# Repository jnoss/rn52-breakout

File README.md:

# rn52-breakout
RN-52 breakout board (Based on Sparkfun's, but adds FTDI header)

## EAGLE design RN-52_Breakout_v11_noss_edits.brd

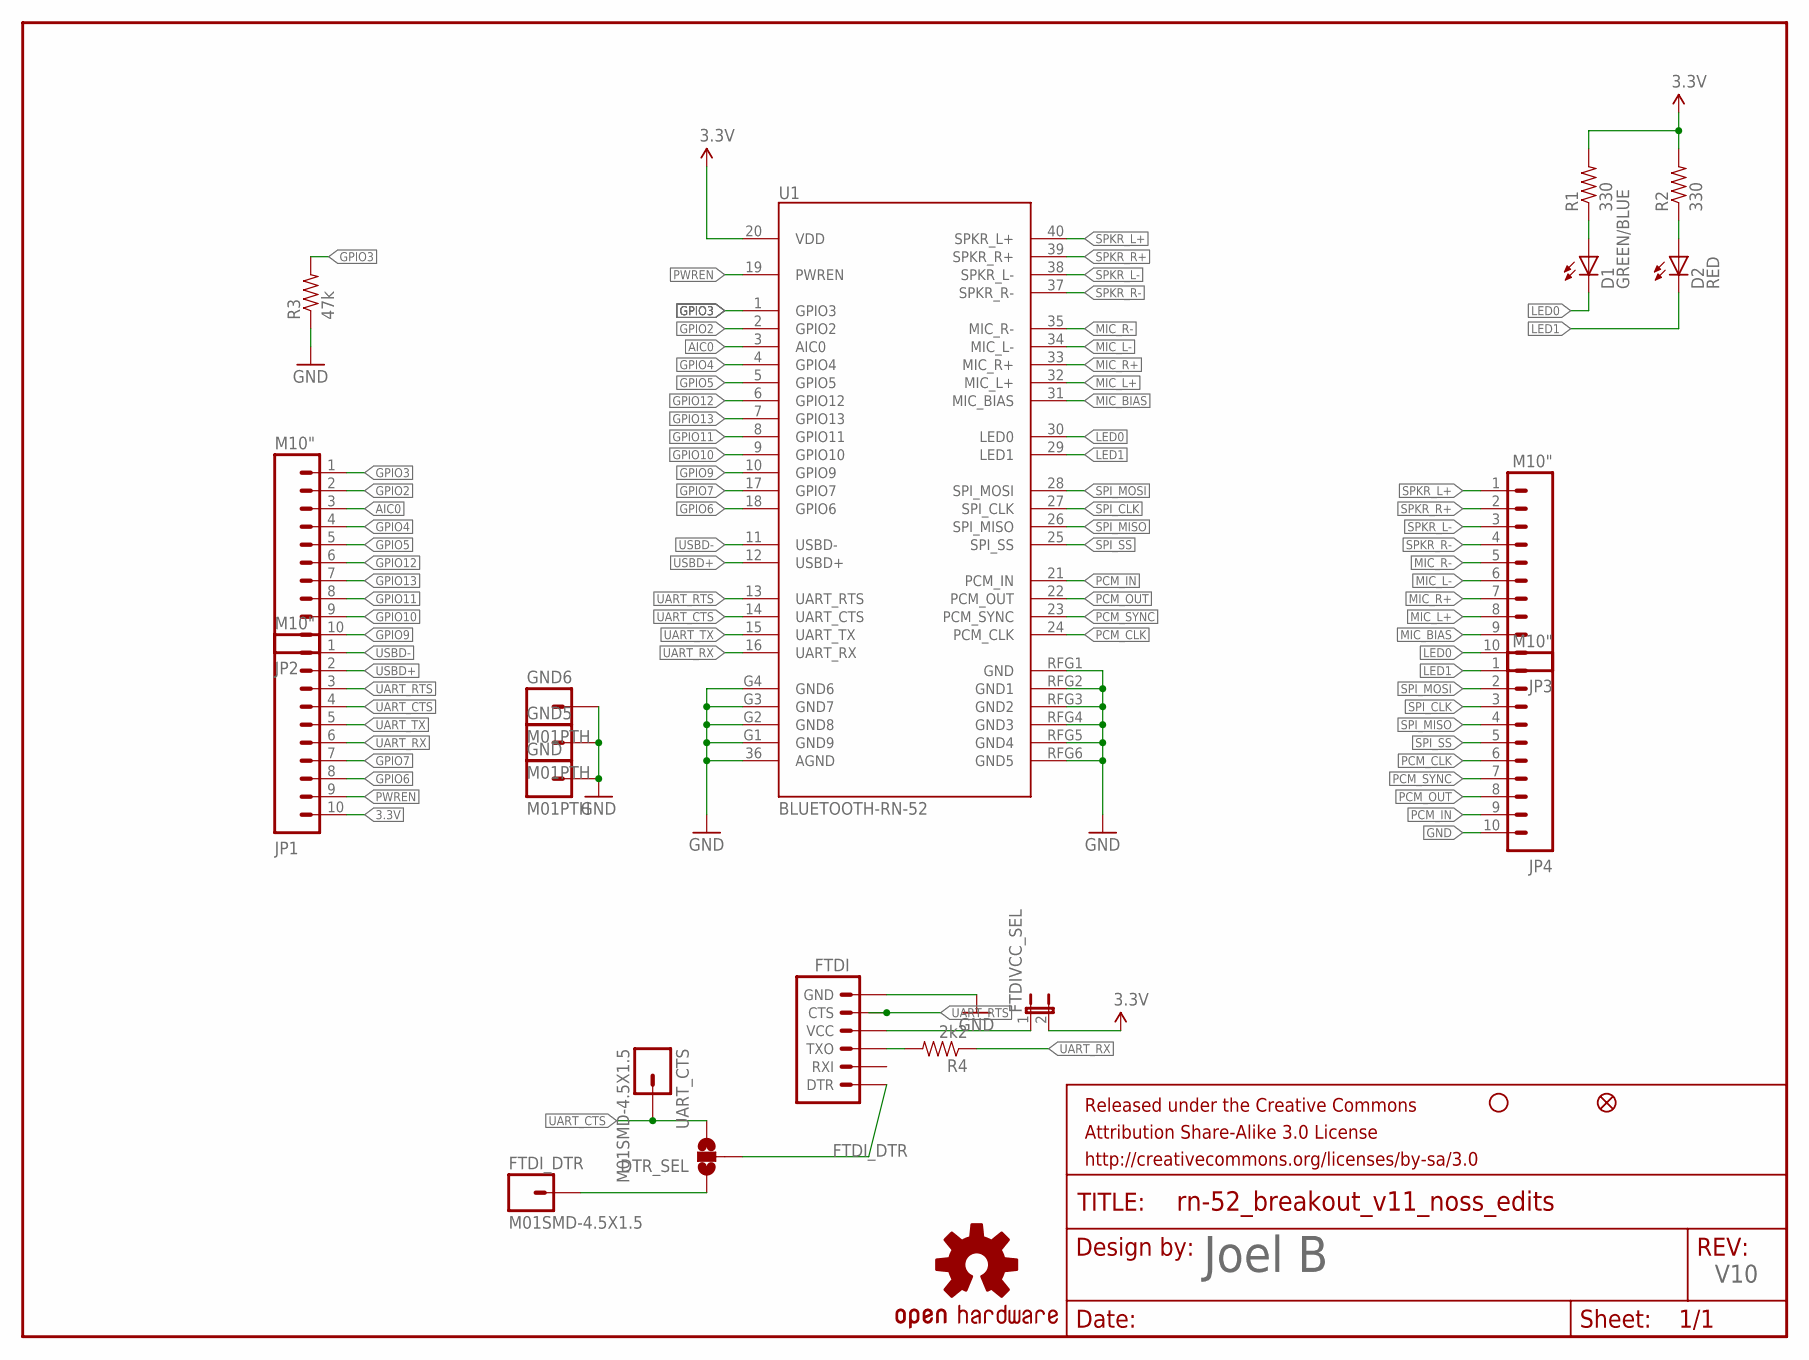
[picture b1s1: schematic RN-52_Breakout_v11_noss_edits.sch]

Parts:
D1: GREEN/BLUE; LED-0603
D2: RED; LED-0603
DTR_SEL: SOLDERJUMPER_2WAYS; SJ_3
FID1: FIDUCIAL1X2; FIDUCIAL-1X2
FRAME1: FRAME-LETTER; CREATIVE_COMMONS
FTDI: ARDUINO_SERIAL_PROGRAMPTH; 1X06
FTDIVCC_SEL: JUMPER-2PTH; 1X02
FTDI_DTR: M01SMD-4.5X1.5; PAD-1.5X4.5
GND, GND5, GND6: M01PTH; 1X01
JP1, JP2, JP3, JP4: M10"; 1X10
LOGO1: OSHW-LOGOS; OSHW-LOGO-S
R1, R2: 330; 0603-RES
R3: 47k; 0603-RES
R4: 2k2; 0603-RES
STANDOFF1: STAND-OFF
U1: BLUETOOTH-RN-52; RN-52
UART_CTS: M01SMD-4.5X1.5; PAD-1.5X4.5

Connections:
3.3V: FTDIVCC_SEL.2, JP1.10, R1.2, R2.2, U1.20 (VDD)
AIC0: JP2.3, U1.3 (AIC0)
FTDI_DTR: DTR_SEL.2, FTDI.1 (DTR)
GND: FTDI.6 (GND), GND.1, GND5.1, GND6.1, JP4.10, R3.1, U1.36 (AGND), U1.G1 (GND9), U1.G2 (GND8), U1.G3 (GND7), U1.G4 (GND6), U1.RFG1 (GND), U1.RFG2 (GND1), U1.RFG3 (GND2), U1.RFG4 (GND3), U1.RFG5 (GND4), U1.RFG6 (GND5)
GPIO2: JP2.2, U1.2 (GPIO2)
GPIO3: JP2.1, R3.2, U1.1 (GPIO3)
GPIO4: JP2.4, U1.4 (GPIO4)
GPIO5: JP2.5, U1.5 (GPIO5)
GPIO6: JP1.8, U1.18 (GPIO6)
GPIO7: JP1.7, U1.17 (GPIO7)
GPIO9: JP2.10, U1.10 (GPIO9)
GPIO10: JP2.9, U1.9 (GPIO10)
GPIO11: JP2.8, U1.8 (GPIO11)
GPIO12: JP2.6, U1.6 (GPIO12)
GPIO13: JP2.7, U1.7 (GPIO13)
LED0: D1.C, JP3.10, U1.30 (LED0)
LED1: D2.C, JP4.1, U1.29 (LED1)
MIC_BIAS: JP3.9, U1.31 (MIC_BIAS)
MIC_L+: JP3.8, U1.32 (MIC_L+)
MIC_L-: JP3.6, U1.34 (MIC_L-)
MIC_R+: JP3.7, U1.33 (MIC_R+)
MIC_R-: JP3.5, U1.35 (MIC_R-)
unnamed: D2.A, R2.1
unnamed: D1.A, R1.1
unnamed: FTDI.4 (VCC), FTDIVCC_SEL.1
unnamed: FTDI.3 (TXO), R4.2
unnamed: DTR_SEL.1, FTDI_DTR.P$1
PCM_CLK: JP4.6, U1.24 (PCM_CLK)
PCM_IN: JP4.9, U1.21 (PCM_IN)
PCM_OUT: JP4.8, U1.22 (PCM_OUT)
PCM_SYNC: JP4.7, U1.23 (PCM_SYNC)
PWREN: JP1.9, U1.19 (PWREN)
SPI_CLK: JP4.3, U1.27 (SPI_CLK)
SPI_MISO: JP4.4, U1.26 (SPI_MISO)
SPI_MOSI: JP4.2, U1.28 (SPI_MOSI)
SPI_SS: JP4.5, U1.25 (SPI_SS)
SPKR_L+: JP3.1, U1.40 (SPKR_L+)
SPKR_L-: JP3.3, U1.38 (SPKR_L-)
SPKR_R+: JP3.2, U1.39 (SPKR_R+)
SPKR_R-: JP3.4, U1.37 (SPKR_R-)
UART_CTS: DTR_SEL.3, JP1.4, U1.14 (UART_CTS), UART_CTS.P$1
UART_RTS: FTDI.5 (CTS), JP1.3, U1.13 (UART_RTS)
UART_RX: JP1.6, R4.1, U1.16 (UART_RX)
UART_TX: JP1.5, U1.15 (UART_TX)
USBD+: JP1.2, U1.12 (USBD+)
USBD-: JP1.1, U1.11 (USBD-)

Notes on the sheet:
Joel B
V10

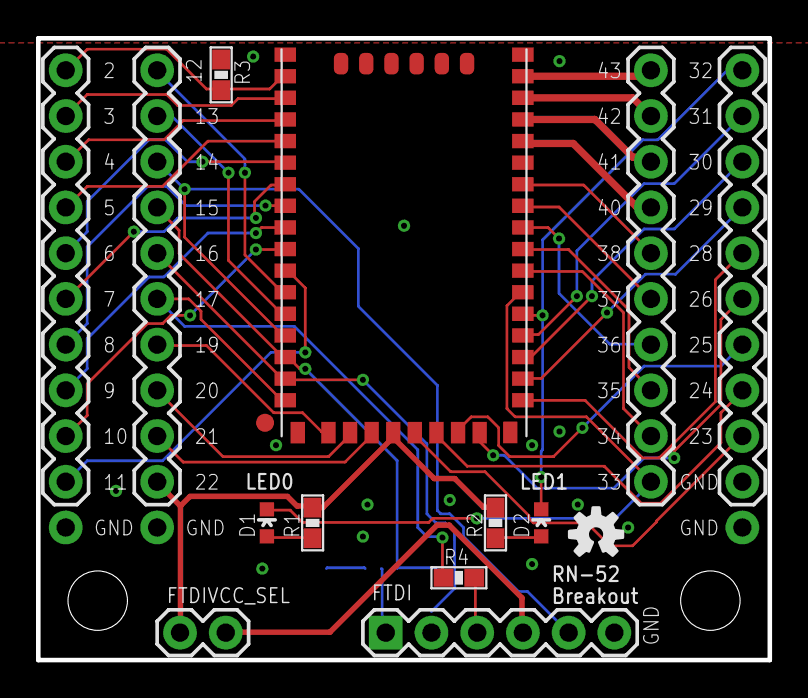
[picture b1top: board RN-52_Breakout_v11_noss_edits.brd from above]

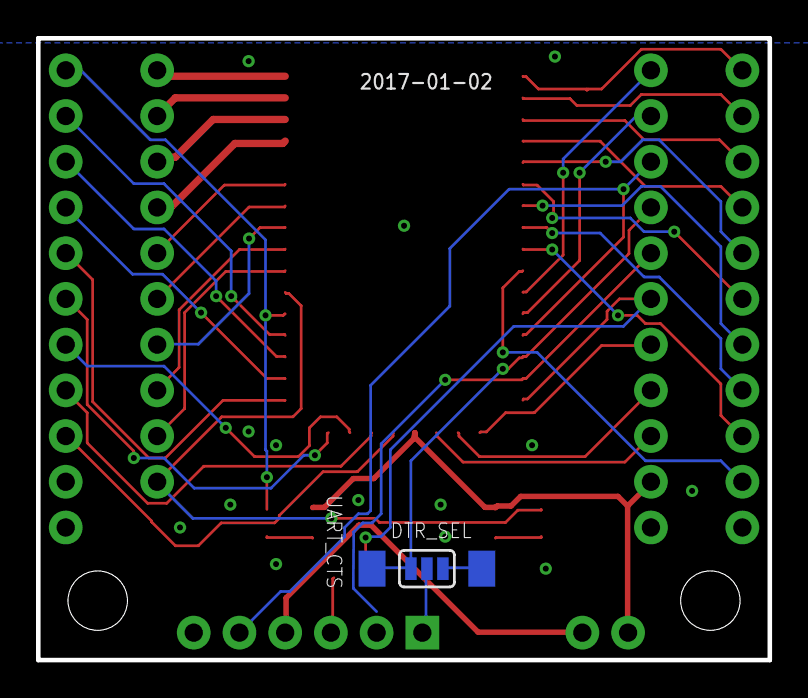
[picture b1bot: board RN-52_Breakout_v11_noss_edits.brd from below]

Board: 2 copper layers, 40.6 x 34.5 mm, 24 parts (3 on the bottom side), 46 nets.

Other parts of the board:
STANDOFF2: STAND-OFF

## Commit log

2017-01-01 gitignore
2017-01-01 sides routed
2017-01-01 eagle preview autogen
2017-01-02 rename no space
2017-01-02 fix spkr out
2017-01-02 fix labels
2017-01-02 center labels
2017-01-02 add ftdi
2017-01-02 move to bottom
2017-01-02 add 2nd mounting hole
2017-01-03 with usb dfu
2017-01-03 wip routing
2017-01-03 wip adding recommendations from datasheet
2017-01-03 routed
2017-01-03 edits for printing
2017-01-03 fix missing connection
2017-01-11 add stencil
2017-01-22 add stencils with shrunken pads
2017-01-24 edit stencils

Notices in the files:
parts and their libraries:
SparkFun-RF: Licensing: CC v3.0 Share-Alike You are welcome to use this library for commercial purposes.
SparkFun-Aesthetics: Released under the Creative Commons Attribution Share-Alike 3.0 License
SparkFun-Aesthetics: http://creativecommons.org/licenses/by-sa/3.0
